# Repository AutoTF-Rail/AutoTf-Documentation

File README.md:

# AutoTF Documentation

## Info

This repo contains the documentation for the AutoTF systems as implemented and is still an active **Work-In-Progress**.

Be aware that the documentation might not reflect the actual code in every corner.

The documentation might lag behind a bit, because the safety and functionality of actively running systems is priorizied.

### **All info given in this repository are without warranty. AutoTF and individiuals representing AutoTF are not liable for any damanges occuring due to the contents unless specified otherwise in a contract.**

## LFS
Large files are hosted on the AutoTF Gitea instance at [lfs.autotf.de](https://lfs.autotf.de/admin/AutoTf-Documentation)

## Active repositories

Active repositories of AutoTF, that contain code that is used in prod are:

### Utility:
* [AutoTf.Logging](https://github.com/AutoTF-Rail/AutoTf.Logging): Logger used in all main AutoTF repo's.
* [AutoTf.YubiKeyInteractor](https://github.com/AutoTF-Rail/AutoTf.YubiKeyInteractor): Interactor to register yubikey's on the central server.
* [AutoTf.MotorCalibration](https://github.com/AutoTF-Rail/AutoTf.MotorCalibration): CLI Tool to calibrate and test motors.
* [Machine-Setup](https://github.com/AutoTF-Rail/Machine-Setup): Commands for a central bridge installation(To be moved to docs repo.)
* [AutoTf.Manager](https://github.com/AutoTF-Rail/AutoTf.Manager): Desktop app to manage the central server and trains.
* [AutoTf.GpsTest](https://github.com/AutoTF-Rail/AutoTf.GpsTest): A very simple console app to get the latitude and longitude as well as speed from a Gps device. (Code is partially used in Central Bridge)
* [AutoTf.FahrplanParser](https://github.com/AutoTF-Rail/AutoTf.FahrplanParser): A console app/package that parses images of a fahrplan into code to be used in automation.
* [AutoTf.Localisation](https://github.com/AutoTF-Rail/AutoTf.Localisation): CLI Demo to localise a train based on train display outputs + Hektometer recognition infront of the train. (Works with [AutoTf.FahrplanParser](https://github.com/AutoTF-Rail/AutoTf.FahrplanParser))
* [CentralBridgeInstall](https://github.com/AutoTF-Rail/CentralBridgeInstall/): Contains scripts used in the install script generated in [AutoTf.Manager](https://github.com/AutoTF-Rail/AutoTf.Manager).
* [AutoTf.AuthentikDashboard](https://github.com/AutoTF-Rail/AutoTf.AuthentikDashboard): API for interactions with the Authentik API for external users. (Includes somewhat working Avalonia WASM frontend).
* [AutoTf.AdminPanel](https://github.com/AutoTF-Rail/AutoTf.AdminPanel): API and Frontend for interactions with cloudflare, docker, plesk, and authentik to create new EVU servers easier.

### Central Code:
* [AutoTf.CentralBridge](https://github.com/AutoTF-Rail/AutoTf.CentralBridge): Backend that runs on the raspberry PI's on a train, that act as a central brain.
* [AutoTf.TabletOS](https://github.com/AutoTF-Rail/AutoTf.TabletOS): Avalonia OS that runs on a tablet to configure and control a central bridge/train.
* [Central Server](https://github.com/AutoTF-Rail/Central-Server): Dockerized central server to remote manage trains.
* [AutoTf.Aic](https://github.com/AutoTF-Rail/AutoTf.Aic): Backend that runs on the AIC (Jetson orin nano super) on a train to handle video streams to detect objects etc.

Please keep in mind that some repositories might not be public yet due to their active development.

## API documentation

Links to the api documentations can be found in [/swagger](https://github.com/AutoTF-Rail/AutoTf-Documentation/tree/main/swagger)

## Drawn Documentation

Documentation is made using Draw.IO and saved in [DrawIODOC](https://github.com/AutoTF-Rail/AutoTf-Documentation/tree/main/DrawIODOC/)

Exports can be found in

### Testing Roadmap:

### Train setup diagram:

### AI Control diagram:

### Open API diagram:

### Infrastructure diagram:

## 3D models

The molds for motors, and other prototyping is done in blender, and all models can be found in [Models](https://github.com/AutoTF-Rail/AutoTf-Documentation/tree/main/Models/).

Rendered screenshots can also be found in the Models folder.

There will always be a printable example version in the [ExampleLever](https://github.com/AutoTF-Rail/AutoTf-Documentation/tree/main/Models/Export/Print/ExampleLever/) folder.

## Licenses

While some repositories are listed under the Apache 2.0 license, main parts like the [CentralBridge](https://github.com/AutoTF-Rail/AutoTf.CentralBridge) are listed under the [GPL](https://www.gnu.org/licenses/gpl-3.0.txt) due to the usage of software/packages of third party listed as well under the GPL license.

For a list of used packages please refer to the individiual repository.

## Contributions

Would you like to contribute to this project, or noticed something wrong?

Feel free to contact us at [opensource@autotf.de](mailto:opensource@autotf.de)

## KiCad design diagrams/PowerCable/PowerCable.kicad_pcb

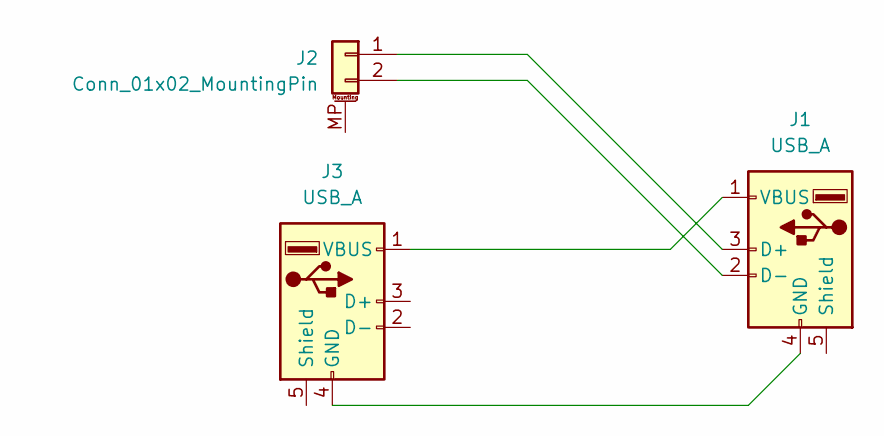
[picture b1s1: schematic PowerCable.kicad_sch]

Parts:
J1, J3: USB_A; USB_A_Molex_67643_Horizontal
J2: Conn_01x02_MountingPin; MountingPin

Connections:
unnamed: J1.3 (D+), J2.1 (TXD)
unnamed: J1.2 (D-), J2.2 (RXD)
unnamed: J1.4 (GND), J3.4 (GND)
unnamed: J1.1 (VBUS), J3.1 (VBUS)

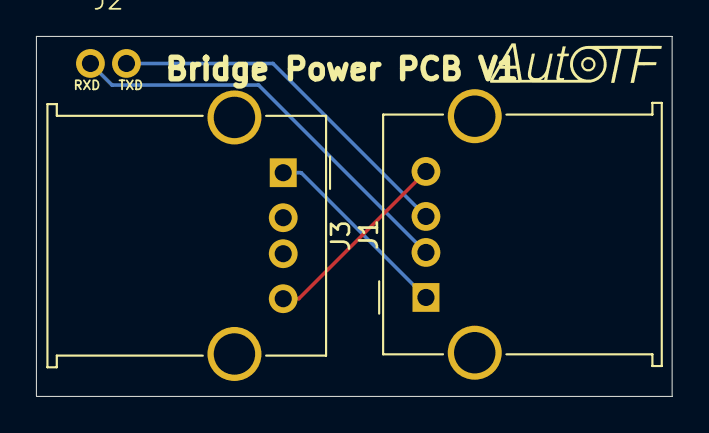
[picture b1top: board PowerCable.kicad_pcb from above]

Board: 2 copper layers, 35.3 x 20.0 mm, 3 parts (0 on the bottom side), 4 nets.

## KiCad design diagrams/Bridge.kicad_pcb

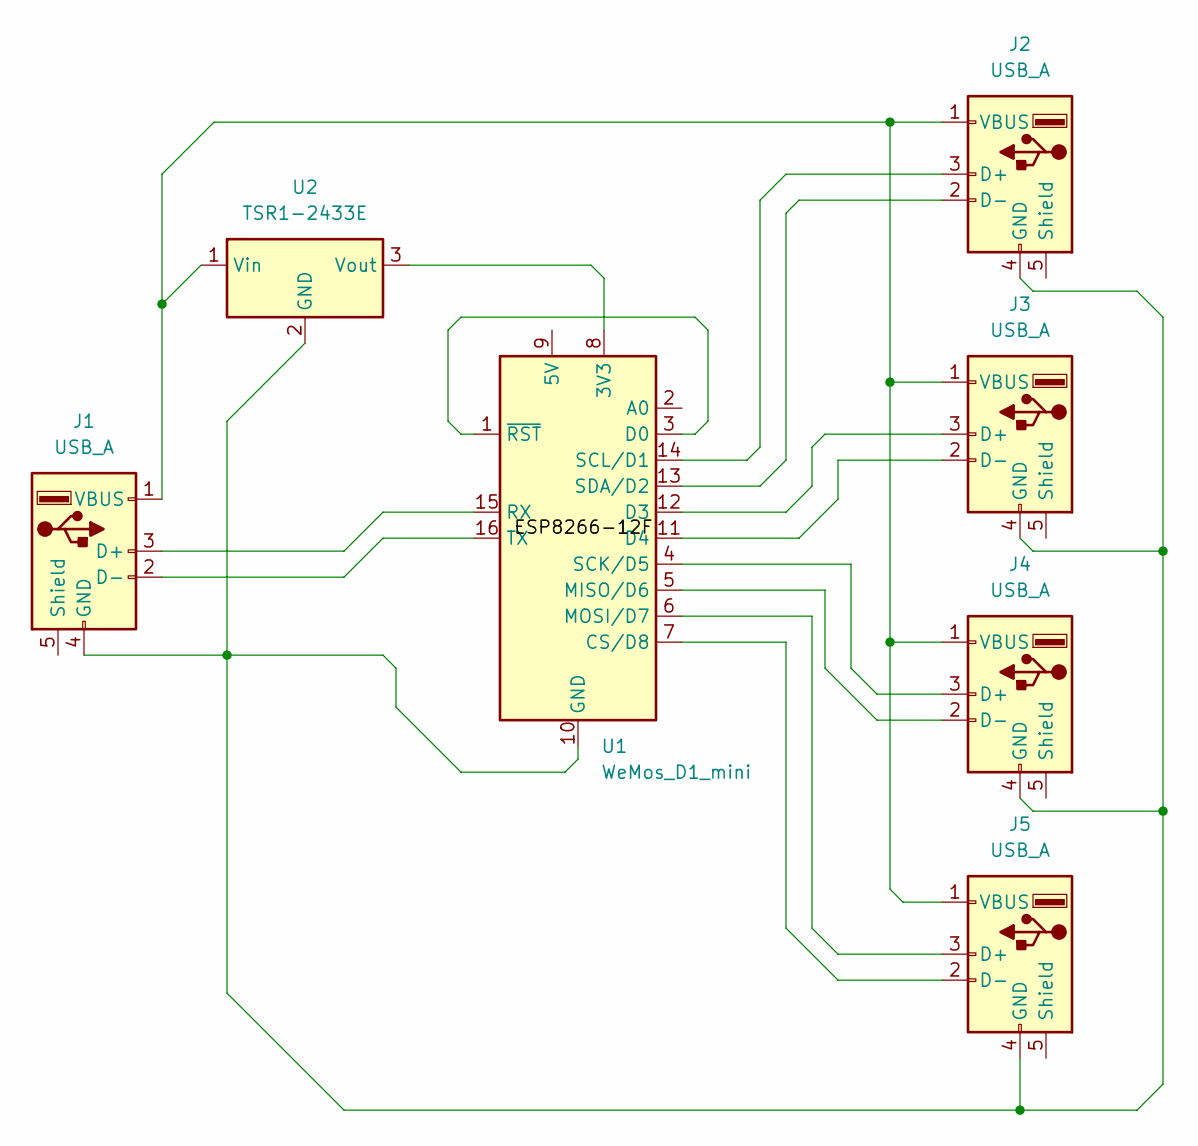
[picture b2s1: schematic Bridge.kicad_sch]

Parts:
J1, J2, J3, J4, J5: USB_A; USB_A_Molex_67643_Horizontal
U1: WeMos_D1_mini; WEMOS_D1_mini_light
U2: TSR1-2433E; Converter_DCDC_TRACO_TSR1-xxxxE_THT

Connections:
unnamed: J1.3 (D+), U1.15 (RX)
unnamed: J1.2 (D-), U1.16 (TX)
unnamed: J1.4 (GND), J2.4 (GND), J3.4 (GND), J4.4 (GND), J5.4 (GND), U1.10 (GND), U2.2 (GND)
unnamed: J1.1 (VBUS), J2.1 (VBUS), J3.1 (VBUS), J4.1 (VBUS), J5.1 (VBUS), U2.1 (Vin)
unnamed: J2.3 (D+), U1.14 (SCL/D1)
unnamed: J2.2 (D-), U1.13 (SDA/D2)
unnamed: J3.3 (D+), U1.12 (D3)
unnamed: J3.2 (D-), U1.11 (D4)
unnamed: J4.3 (D+), U1.4 (SCK/D5)
unnamed: J4.2 (D-), U1.5 (MISO/D6)
unnamed: J5.3 (D+), U1.6 (MOSI/D7)
unnamed: J5.2 (D-), U1.7 (CS/D8)
unnamed: U1.8 (3V3), U2.3 (Vout)
unnamed: U1.1 (~RST), U1.3 (D0)

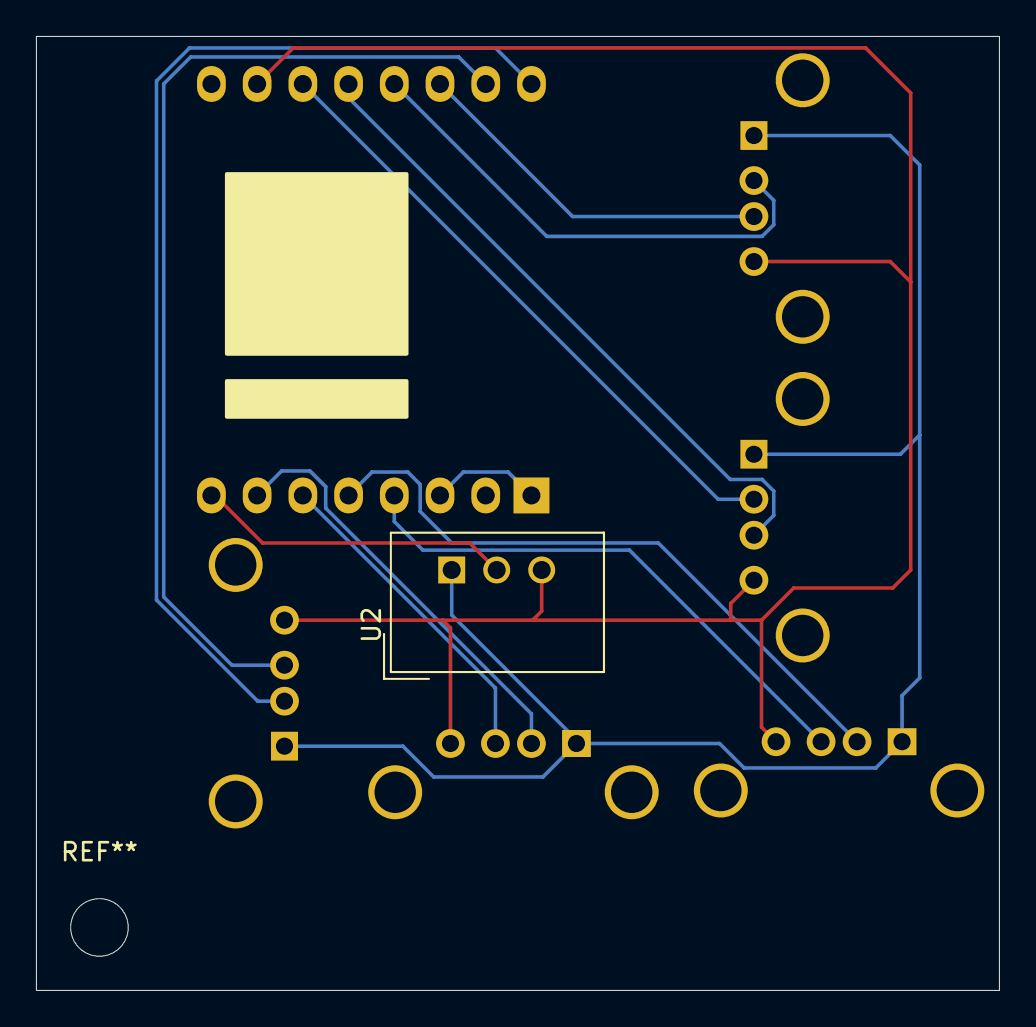
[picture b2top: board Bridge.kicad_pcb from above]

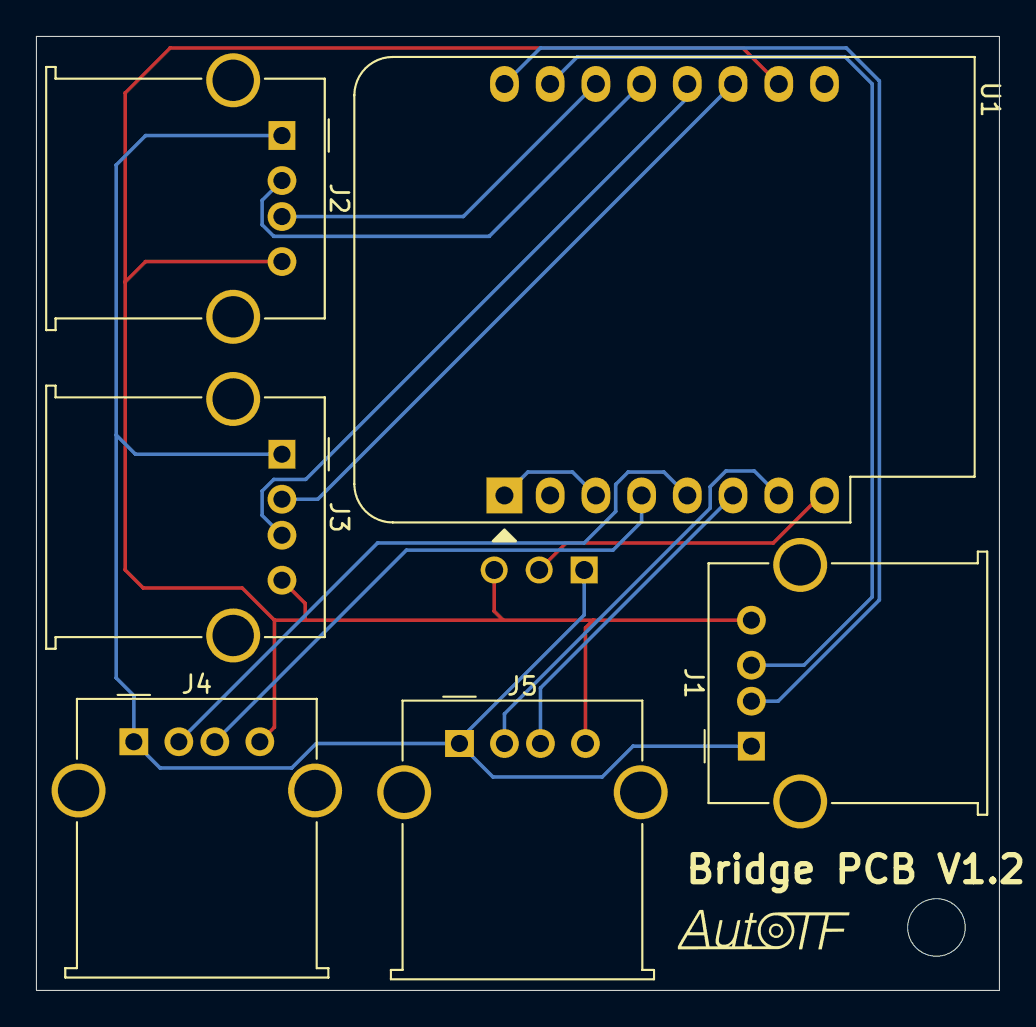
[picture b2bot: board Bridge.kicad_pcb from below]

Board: 2 copper layers, 53.5 x 53.0 mm, 7 parts (6 on the bottom side), 14 nets.

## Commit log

2024-11-04 First throw
2024-11-04 moved to folder
2024-11-05 symb library
2024-11-09 Redesigned bridge
2025-01-16 Added drawio diagrams and circuits
2025-03-16 Removed PCB diagrams (not used anymore), updated doc diagrams and added Lever example model
2025-03-16 Added exported models for 3D printing the example lever
2025-03-16 Added WIP Model
2025-03-16 Fixed readme paths
2025-03-16 Actually fixed links
2025-03-16 Added active repositories
2025-03-19 Updated disclaimer
2025-03-20 Added PZB levers base
2025-03-24 Added display examples
2025-03-31 Made several optimizations to the example lever mountings (TO BE EXPORTED)
2025-04-01 Added spine for camera holder for displays
2025-04-01 Small info
2025-04-03 Small changes to display spider
2025-04-08 Minor display spider changes
2025-04-08 Updated readme, and added exported images
2025-04-08 fixed image links
2025-04-08 Updated OpenApi to display the ebula endpoints, and removed some outdated docs
2025-04-09 Updaed the openApi docs
2025-04-09 Added export script, and updated the exports
2025-04-09 Updated export script, and moved drawio files to seperate folder
2025-04-09 Added endpoints on ebula for state retreival
2025-04-09 Added custom command to export docs
2025-04-09 Auto export of documentation.
2025-04-09 Minor changes to ebula
2025-04-10 Seperated ebula controller into timetable and localisation controller
2025-04-10 Added lock states and manual scan endpoints to ebula controller
2025-04-12 Build new spider for new camera
2025-04-14 Made some infos more up to date
2025-04-16 Added example redoc docs
2025-04-16 redoc test
2025-04-16 Other redoc test
2025-04-16 Updated openapi.yaml
2025-04-16 Updated central server docs
2025-04-16 added base for central bridge docs
2025-04-16 Renamed redoc folder to swagger
2025-04-16 Added swagger.md
2025-04-16 Fixed swagger linking
2025-04-16 renamed swagger doc
2025-04-16 Updated central server docs to be up to date
2025-04-16 Renamed some endpoints
2025-04-17 Removed unused file
2025-04-17 Updated centralbridge docs
2025-04-17 Updated central server description
2025-04-17 Added mac auth to central bridge docs
2025-04-17 Removed api reference from drawio docs (replaced with swagger)
2025-04-17 Fixed rendering for some endpoints
2025-04-17 Minor screen spider optimizations
2025-04-18 Added basic infrastructure diagram
2025-04-18 Added example image of train management
2025-04-21 Updated central server documentation
2025-04-21 Updated new key endpoint parameters
2025-04-23 Added base for aic docs
2025-04-23 updated Aic doc
2025-04-24 Updated central bridge docs
2025-04-24 Added isEasyControlAvailable endpoint to central bridge
2025-04-25 Added aic information controller
2025-04-25 Added aic information controller to central bridge docs
2025-04-25 Updated central bridge link
2025-04-25 Added evuname endpoint
2025-05-08 Added traincount endpoint
2025-05-09 added allowedTrainsCount endpoint for centralserver
2025-05-10 Added WIP flirt rebuild
2025-05-15 Updated flirt rebuild export
2025-05-15 WIP flirt rebuild
2025-05-17 Updated flirt rebuild
2025-05-17 Added rendered flirt 3 images
2025-05-17 Fixed screenshot links
2025-05-20 Added testing roadmap
2025-05-20 Added power cut point
2025-05-21 Added roadmap to readme
2025-05-22 near finished flirt rebuild
2025-05-22 Added lfs config
2025-05-22 Added blender files
2025-05-22 Test change
2025-05-22 Updated lfs url
2025-05-22 test push
2025-05-22 Hopefully fixed lfs url?
2025-05-22 Minor changes to push to new lfs
2025-05-23 lfs test change
2025-05-24 Added and updated holder for example (printable) lever for flirt 3
2025-05-25 Added physical switch casing
2025-05-26 Updated central bridge API docs
2025-05-28 Added powerboard base
2025-06-06 collection organisation
